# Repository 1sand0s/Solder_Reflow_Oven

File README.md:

<h1>Solder Reflow Oven Controller (2014)</h1>

<h2>Contents</h2>
<h4>About</h4>
<h4>Workflow</h4>
<h4>Procedure and Trial</h4>
<h4>Math Modelling of Toaster Oven</h4>

<h3>About</h3>
I built this during my fifth semester course on control systems. It uses a AT90USB646 mcu to implement PID along with a AD595AQ temperature sensor.
This PCB was built at home using the PCB toner transfer method and hydrochloric acid/hydrogen peroxide as etchant. I hadn't found time to write a detailed procedure and stuff , so here goes

<h3>Workflow</h3>

First up is the inventory . As for components , I have chosen ones which were readily available except for AT90USB646 which I wanted to experiment with for a long time .I have chosen AT90USB646 since the LUFA project by Dean Camera comes with examples of AT90USB1287 which is very similar to AT90USB646 for implementing the USB stack . I have included a transistor to drive the relay however for the relay i'm using this wasn't necessary since the AT90USB646 can source upto 40mA of current per I/O whereas the relay only needed 20mA but the relays you might use might be different hence the transistor.Okay , lets jump in then

For the toner transfer , after a few tries I experienced better results when after scrubbing the copper surface with steel wool I left the surface damp with surgical spirit and stuck the glossy paper to it and then proceeded with ironing it.

I used a HP Laserjet M1005 printer and Oddy Photo Glossy Paper. I was initially apprehensive about using this glossy paper since its meant for inkjet but I have used it several times since writing this and its never caused any damage to my printer and the paper peels right off after ironing, leaving behind an excellent finish(note: I changed the crystal footprint to SMD since I realized I had a few left from a previous experiment)

We interrupt this post to bring you a brief review of chemistry to understand why this works !

Before this venture , lets clear some terminologies 

Reduction :- In basic terms refers to an element/compound accepting the hydrogen ion/proton (hydrogen with its single valence electron removed)

Octet/Duplet :- Every element tries to achieve this stable configuration where it has 8 electrons in its valence shell if it has more than 1 shell whereas it tries to achieve a config with 2 electrons if it has a singe shell. 

Covalent Bonds :- The above Octet/Duplet is normally achieved by forming bonds where the elements share one or more of their valence electrons . These bonds are called Covalent bonds.

Dipole Moment :- In covalent bonds , the electrons may not be shared equally . They may be drawn more towards one of the participating elements . Since electrons by definition represent -ve charge, the element towards which it is drawn becomes slightly -vely charged and the other becomes slightly +vely charged.

Okay , now to the chemical reactions.

The hydrochloric acid has a covalent bond formed between hydrogen which requires an electron to become duplet and chlorine which also requires a single electron to achieve octet . However , the electrons are drawn more toward chlorine thereby making this bond polarized . This polarization makes HCL a pretty good acid since the slightly positive hydrogen has a tendancy to migrate from this HCL bond and attack other electronegative centres thus reducing them .

Now, lets examine our hydrogen peroxide molecule . It has a covalent bond between two oxygen atoms and each of these oxygen atoms forms a covalent bond with hydrogen atoms . Thus , every atom in this molecule has achieved either a duplet or octet and thus the molecule is stable. However , like in our previous case , the peroxide molecule is polarized . Of-course there is no fight between the oxygen atoms since they are identical in every aspect but between the oxygen and hydrogen . Except that this dipole moment is stronger than that of HCL. This provides the loosely bound hydrogen with a more electronegative oxygen to be attracted to , as a result hydrogen and chlorine covalent bond dissociate with the hydrogen attacking the peroxide linkage resulting in formation of water molecules while the copper on the PCB surface reacts with chlorine to form copper(II)chloride through ionic bond . (Note:- The bigger +ve and -ve imply stronger dipole moment/charge induction)

<h3>Procedure and Trial</h3>

 Watch what your doing ya fool!

You want to get into a situation where you control the etching rate by adding hydrogen peroxide and not the acid .First , dilute the acid . LR grade HCL ships with 35-38% conc and in HCL terms that means very highly concentrated so treat it with respect , its real nasty stuff . Take a beaker and add about 150ml of water (preferably boiled and cooled but no fuss) , add to this about 10-12ml HCl using a bulb pipette . Don't mouth pipette , HCL fumes are nasty too . With this setup , slowly add hydrogen peroxide . HCL does not react with copper as it is since as we learnt in the previous section to break HCL bond we need a stronger electronegative centre than chlorine which is provided by oxygen of hydrogen peroxide(the dilution does cause the formation of hydronium ions but cuprous ions being below hydrogen in the reactivity series aren't very good in displacing hydrogen from HCL). 
So carefully add hydrogen peroxide in steps of 5ml with max quantity being around 15-25ml. Do not exceed this . For your sake , I have done it and added in a very high conc of HCl and H2O2 and as the below video shows , its not very pleasant.

 Video of what happens when you add excess HCl and H2O2

Now coming back ,with each 5ml addition of peroxide you should observe the etching rate increase . When around 25ml of peroxide has been added , stop and stir with a glass rod . Stirring once again increases the etching rate . I usually do a trial with a spare bit of board before trying it on the actually design . This is how it went and you can see the etching rate increase with each addition of peroxide.

Video of controlling etching rate with controlled addition of H2O2

Final result of trial 

Now for the real thing . 

Video of the final design etching

Most forums tell you that its possible to remove the toner with spirit but I tried and its pretty hard . On the other hand with acetone its a piece of cake. Finally 

To protect the board and to make it easier for soldering , I used <a href="https://erp.suntechcircuits.com/reffile/035C1F2C-AFB7-4E42-BFAE-1057683B9CB5.pdf">KSM-s6189</a> as the soldermak . This is a photoimageable ink and works slightly differently than the traditional UV soldermsk in that it requires to be pre-heated to 75 degree celsius before UV exposure followed by developing in an aqueos solution of sodium/potassium carbonate (I used cooking soda which is sodium bicarbonate but it worked fine)  and post-heated to 150 degree celsius post exposure and development.Exposing the board

The final board.

<h3>Math Modelling of Toaster Oven</h3>

Dealing with linear systems in control systems is a lot easier than with non-linear system . To prove an approximate linear relation arguement I started by turning on the toaster oven for 10 minutes and measured the AD595 output voltage by using the ADC on an arduino and plotted the data against time in Matlab. From AD595 datasheet the relation between temperature and AD595 output is linear and from the graph below we can see that the relation between the output voltage of AD595 and time is also linear therefore we can conclude that the rise in temperature of the toaster oven against time is also linear(an approximation but it makes things a lot easier)

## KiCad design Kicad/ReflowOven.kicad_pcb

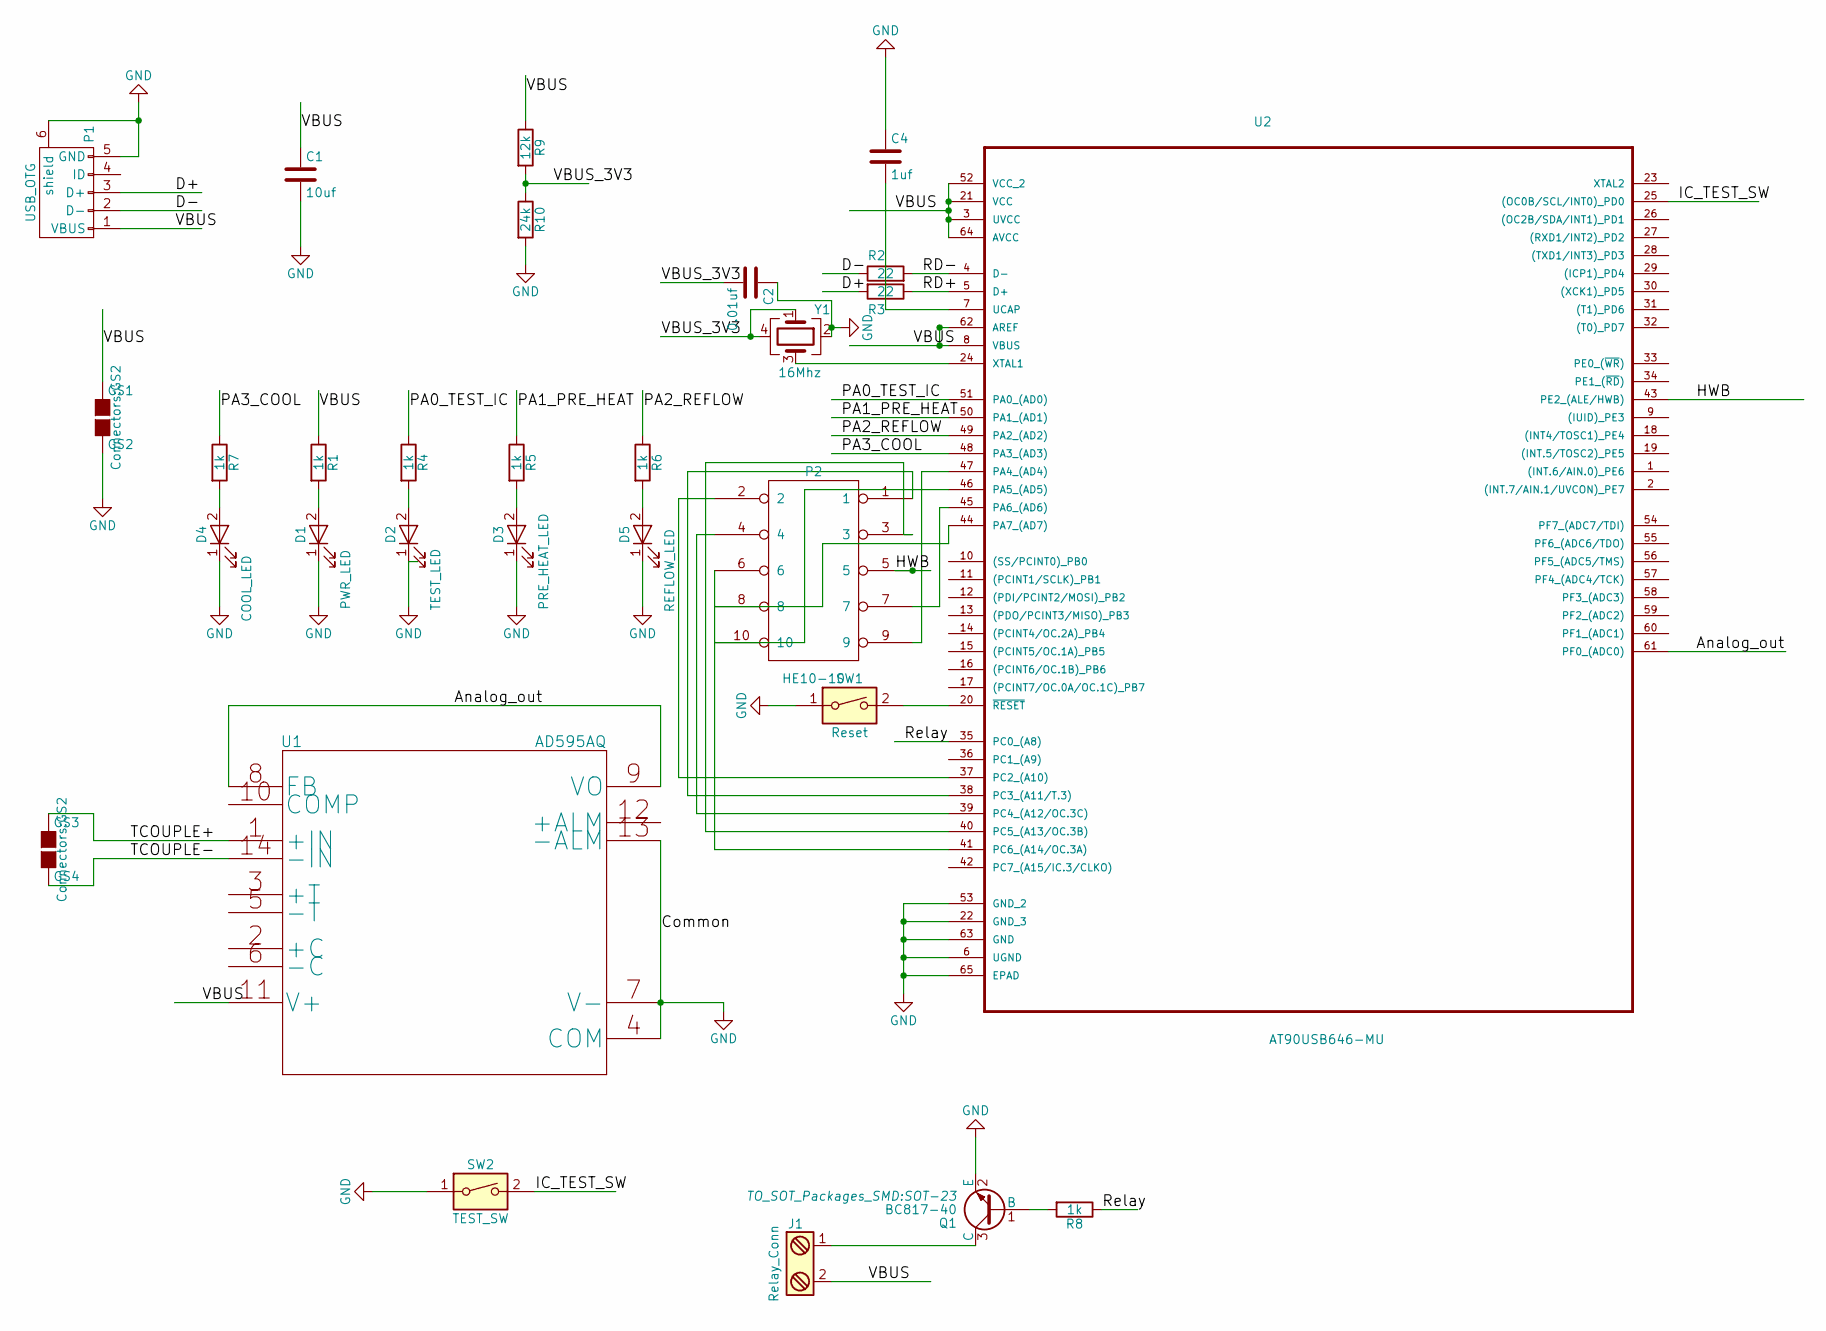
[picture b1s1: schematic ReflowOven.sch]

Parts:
C1: 10uf; C_0805_HandSoldering
C2: 0.01uf; C_0805_HandSoldering
C4: 1uf; C_0805_HandSoldering
D1: PWR_LED; LED_0805
D2: TEST_LED; LED_0805
D3: PRE_HEAT_LED; LED_0805
D4: COOL_LED; LED_0805
D5: REFLOW_LED; LED_0805
GS1: GS2
GS3: GS4; GS2
J1: Relay_Conn; bornier2
P1: USB_OTG; USB_MICRO
P2: HE10-10; he10-10d
Q1: BC817-40; SOT-23
R1, R4, R5, R6, R7, R8: 1k; R_0805_HandSoldering
R2, R3: 22; R_0805_HandSoldering
R9: 12k; R_0805_HandSoldering
R10: 24k; R_0805_HandSoldering
SW1: Reset; SW_DIP_x1_W8.61mm_Slide_LowProfile
SW2: TEST_SW; SW_DIP_x1_W8.61mm_Slide_LowProfile
U1: AD595AQ
U2: AT90USB646-MU; TQFP-64_14x14mm_Pitch0.8mm
Y1: 16Mhz; Crystal_SMD_3225-4pin_3.2x2.5mm_HandSoldering

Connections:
/Analog_out: U1.8 (FB), U1.9 (VO), U2.61 (PF0_(ADC0))
/D+: P1.3 (D+), R3.2
/D-: P1.2 (D-), R2.1
/HWB: P2.5, U2.43 (PE2_(ALE/HWB))
/IC_TEST_SW: SW2.2, U2.25 ((OC0B/SCL/INT0)_PD0)
/PA0_TEST_IC: R4.1, U2.51 (PA0_(AD0))
/PA1_PRE_HEAT: R5.1, U2.50 (PA1_(AD1))
/PA2_REFLOW: R6.1, U2.49 (PA2_(AD2))
/PA3_COOL: R7.1, U2.48 (PA3_(AD3))
/RD+: R3.1, U2.5 (D+)
/RD-: R2.2, U2.4 (D-)
/Relay: R8.1, U2.35 (PC0_(A8))
/TCOUPLE+: GS3.1 (G1), U1.1 (+IN)
/TCOUPLE-: GS3.2 (G2), U1.14 (-IN)
/VBUS: C1.1, GS1.1 (G1), J1.2, P1.1 (VBUS), R1.1, R9.1, U1.11 (V+), U2.3 (UVCC), U2.8 (VBUS), U2.21 (VCC), U2.52 (VCC_2), U2.62 (AREF), U2.64 (AVCC)
/VBUS_3V3: C2.2, R9.2, R10.1, Y1.1, Y1.4
GND: C1.2, C2.1, C4.1, D1.1 (K), D2.1 (K), D3.1 (K), D4.1 (K), D5.1 (K), GS1.2 (G2), P1.5 (GND), P1.6 (shield), Q1.2 (E), R10.2, SW1.1, SW2.1, U1.4 (COM), U1.7 (V-), U1.13 (-ALM), U2.6 (UGND), U2.22 (GND_3), U2.53 (GND_2), U2.63 (GND), U2.65 (EPAD), Y1.2
unnamed: C4.2, U2.7 (UCAP)
unnamed: D1.2 (A), R1.2
unnamed: D2.2 (A), R4.2
unnamed: D3.2 (A), R5.2
unnamed: D4.2 (A), R7.2
unnamed: D5.2 (A), R6.2
unnamed: J1.1, Q1.3 (C)
unnamed: P2.1, U2.38 (PC3_(A11/T.3))
unnamed: P2.2, U2.37 (PC2_(A10))
unnamed: P2.3, U2.40 (PC5_(A13/OC.3B))
unnamed: P2.4, U2.39 (PC4_(A12/OC.3C))
unnamed: P2.6, U2.41 (PC6_(A14/OC.3A))
unnamed: P2.7, U2.45 (PA6_(AD6))
unnamed: P2.8, U2.44 (PA7_(AD7))
unnamed: P2.9, U2.47 (PA4_(AD4))
unnamed: P2.10, U2.46 (PA5_(AD5))
unnamed: Q1.1 (B), R8.2
unnamed: SW1.2, U2.20 (~RESET)
unnamed: U2.24 (XTAL1), Y1.3

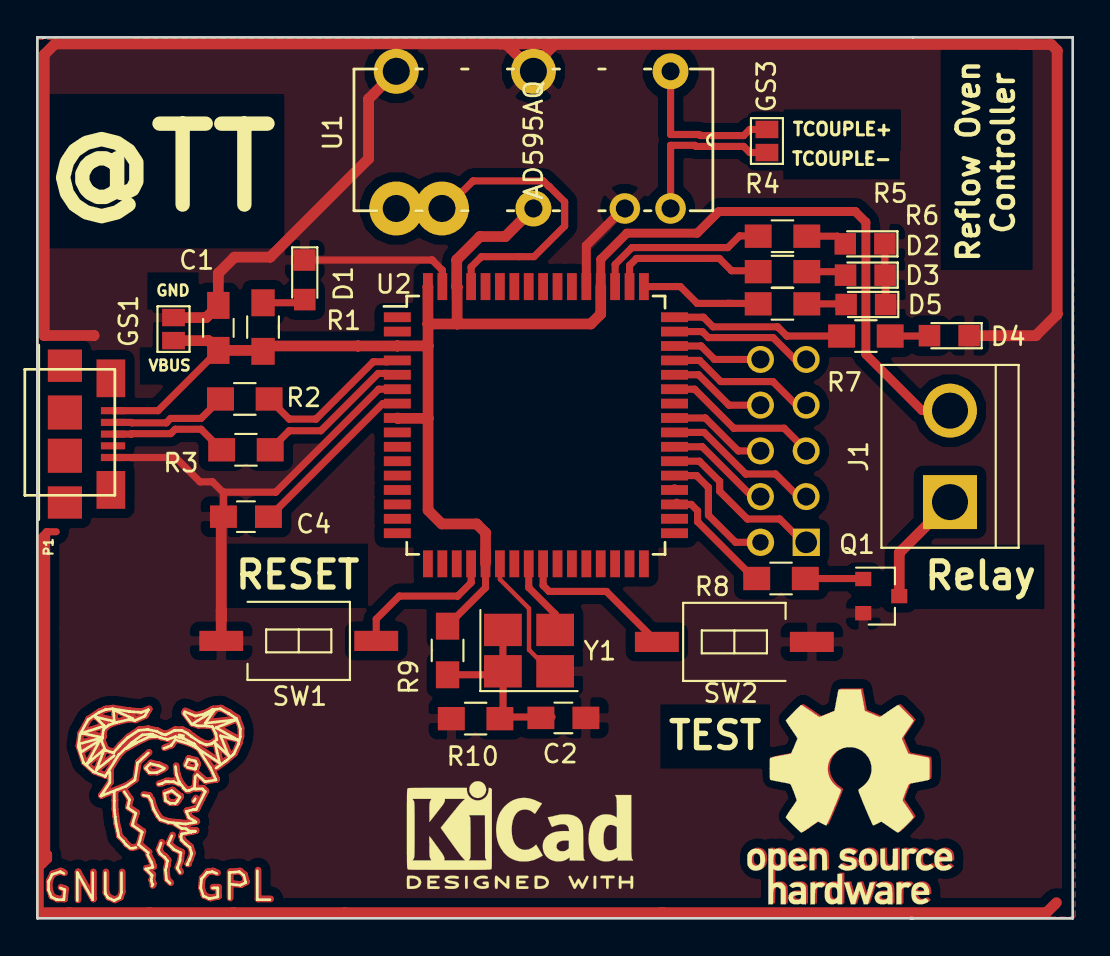
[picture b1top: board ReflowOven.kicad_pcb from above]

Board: 2 copper layers, 57.5 x 48.9 mm, 28 parts (0 on the bottom side), 26 nets.

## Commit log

2017-06-29 Update LICENSE
2017-06-29 Hardware Files for Kicad
2017-06-29 Cad Model of PCB
2017-06-29 Added pads for TCOUPLE
2017-08-04 Modified Files
